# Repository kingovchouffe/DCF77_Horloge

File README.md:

# DCF77_Horloge
 This repos contains the hardware of a DCF77 based clock featuring a STM32F302, an e-ink display, 18650 battery powered with temp humidity and current measurement as well as voltage measurement on the battery.

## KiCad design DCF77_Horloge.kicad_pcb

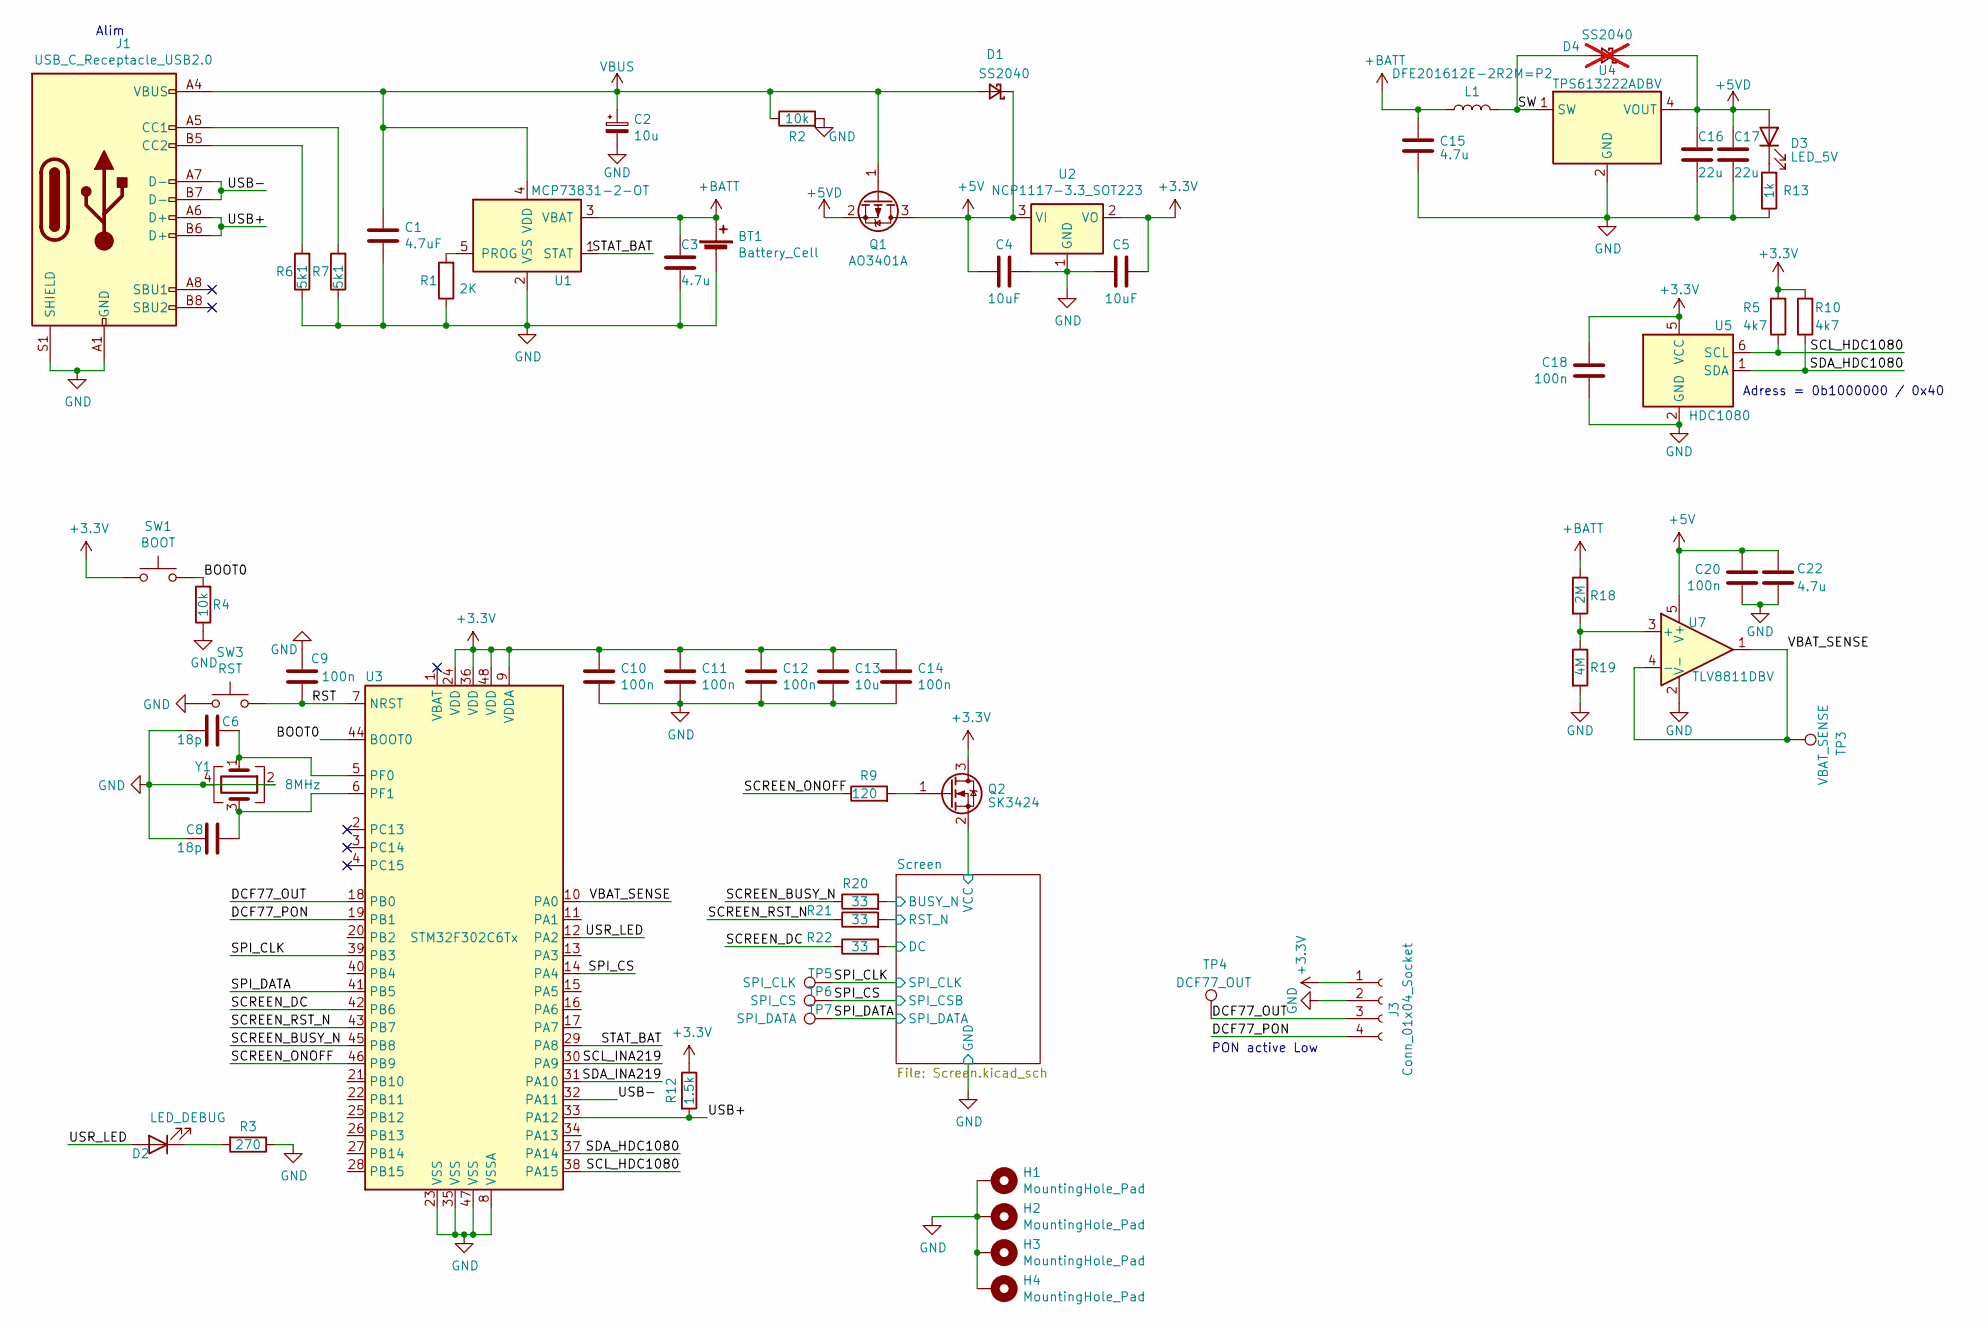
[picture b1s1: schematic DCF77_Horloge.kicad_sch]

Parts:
BT1: Battery_Cell; BatteryHolder_Keystone_1042_1x18650
C1: 4.7uF; C_0603_1608Metric
C2: 10u; CP_Elec_5x5.4
C3, C15, C22: 4.7u; C_0603_1608Metric
C4, C5: 10uF; C_0603_1608Metric
C6, C8: 18p; C_0603_1608Metric
C9, C10, C11, C12, C14, C18, C20: 100n; C_0603_1608Metric
C13: 10u; C_0603_1608Metric
C16, C17: 22u; C_0805_2012Metric
D1: SS2040; D_SOD-123
D2: LED_DEBUG; LED_0603_1608Metric
D3: LED_5V; LED_0603_1608Metric
D4: SS2040; D_SOD-123; not fitted
H1, H2, H3, H4: MountingHole_Pad; MountingHole_3mm_Pad_Via
J1: USB_C_Receptacle_USB2.0; USB_C_Receptacle_GCT_USB4105-xx-A_16P_TopMnt_Horizontal
J3: Conn_01x04_Socket; PinHeader_1x04_P2.54mm_Vertical_SMD_Pin1Left
L1: DFE201612E-2R2M=P2; L_0805_2012Metric_Pad1.15x1.40mm_HandSolder
Q1: AO3401A; SOT-23
Q2: SK3424; SC-59
R1: 2K; R_0603_1608Metric
R2, R4: 10k; R_0603_1608Metric
R3: 270; R_0603_1608Metric
R5, R10: 4k7; R_0603_1608Metric
R6, R7: 5k1; R_0603_1608Metric
R9: 120; R_0603_1608Metric
R12: 1.5k; R_0603_1608Metric
R13: 1k; R_0603_1608Metric
R18: 2M; R_0603_1608Metric
R19: 4M; R_0603_1608Metric
R20, R21, R22: 33; R_0603_1608Metric
SW1: BOOT; SW_SPST_CK_RS282G05A3
SW3: RST; SW_SPST_CK_RS282G05A3
TP3: VBAT_SENSE; TestPoint_Pad_D1.0mm
TP4: DCF77_OUT; TestPoint_Pad_D1.0mm
TP5: SPI_CLK; TestPoint_Pad_D1.0mm
TP6: SPI_CS; TestPoint_Pad_D1.0mm
TP7: SPI_DATA; TestPoint_Pad_D1.0mm
U1: MCP73831-2-OT; SOT-23-5
U2: NCP1117-3.3_SOT223; SOT-223-3_TabPin2
U3: STM32F302C6Tx; LQFP-48_7x7mm_P0.5mm
U4: TPS613222ADBV; SOT-23-5
U5: HDC1080; Texas_PWSON-N6
U7: TLV8811DBV; SOT-23-5
Y1: 8MHz; Crystal_SMD_5032-4Pin_5.0x3.2mm

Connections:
+5V: C4.2, C20.1, C22.1, D1.1 (K), Q1.3 (D), U2.3 (VI), U7.5 (V+)
+5VD: C16.1, C17.1, D3.2 (A), D4.1 (K), Q1.2 (S), U4.4 (VOUT)
+BATT: BT1.1 (+), C3.1, C15.1, L1.1, R18.1, U1.3 (VBAT)
/BOOT0: R4.2, SW1.2, U3.44 (BOOT0)
/DCF77_OUT: J3.3, TP4.1, U3.18 (PB0)
/DCF77_PON: J3.4, U3.19 (PB1)
/RST: C9.1, SW3.2, U3.7 (NRST)
/SCL_HDC1080: R5.1, U3.38 (PA15), U5.6 (SCL)
/SCL_INA219: U3.30 (PA9)
/SCREEN_BUSY_N: R20.1, U3.45 (PB8)
/SCREEN_DC: R22.1, U3.42 (PB6)
/SCREEN_ONOFF: R9.1, U3.46 (PB9)
/SCREEN_RST_N: R21.1, U3.43 (PB7)
/SDA_HDC1080: R10.1, U3.37 (PA14), U5.1 (SDA)
/SDA_INA219: U3.31 (PA10)
/SPI_CLK: TP5.1, U3.39 (PB3); also elsewhere on the board
/SPI_CS: TP6.1, U3.14 (PA4); also elsewhere on the board
/SPI_DATA: TP7.1, U3.41 (PB5); also elsewhere on the board
/STAT_BAT: U1.1 (STAT), U3.29 (PA8)
/SW: D4.2 (A), L1.2, U4.1 (SW)
/Screen/BUSY_N: R20.2; also elsewhere on the board
/Screen/DC: R22.2; also elsewhere on the board
/Screen/RST_N: R21.2; also elsewhere on the board
/USB+: J1.A6 (D+), J1.B6 (D+), R12.2, U3.33 (PA12)
/USB-: J1.A7 (D-), J1.B7 (D-), U3.32 (PA11)
/USR_LED: D2.2 (A), U3.12 (PA2)
/VBAT_SENSE: TP3.1, U3.10 (PA0), U7.1, U7.4 (-)
GND: BT1.2 (-), C1.2, C2.2, C3.2, C4.1, C5.2, C6.2, C8.2, C9.2, C10.2, C11.2, C12.2, C13.2, C14.2, C15.2, C16.2, C17.2, C18.2, C20.2, C22.2, H1.1, H2.1, H3.1, H4.1, J1.A1 (GND), J1.A12 (GND), J1.B1 (GND), J1.B12 (GND), J1.S1 (SHIELD), J3.2, R1.1, R2.2, R3.1, R4.1, R6.1, R7.1, R13.1, R19.2, SW3.1, U1.2 (VSS), U2.1 (GND), U3.8 (VSSA), U3.23 (VSS), U3.35 (VSS), U3.47 (VSS), U4.2 (GND), U5.2 (GND), U7.2 (V-), Y1.2, Y1.4; also elsewhere on the board
unnamed: D2.1 (K), R3.2
unnamed: D3.1 (K), R13.2
unnamed 31: Q2.2 (S); also elsewhere on the board
unnamed: J1.A5 (CC1), R7.2
unnamed: J1.B5 (CC2), R6.2
unnamed: R1.2, U1.5 (PROG)
unnamed: C6.1, U3.5 (PF0), Y1.1
unnamed: C8.1, U3.6 (PF1), Y1.3
unnamed: R18.2, R19.1, U7.3 (+)
VBUS: C1.1, C2.1, D1.2 (A), J1.A4 (VBUS), J1.A9 (VBUS), J1.B4 (VBUS), J1.B9 (VBUS), Q1.1 (G), R2.1, U1.4 (VDD)

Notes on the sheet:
PON active Low
Adress = 0b1000000 / 0x40
Alim

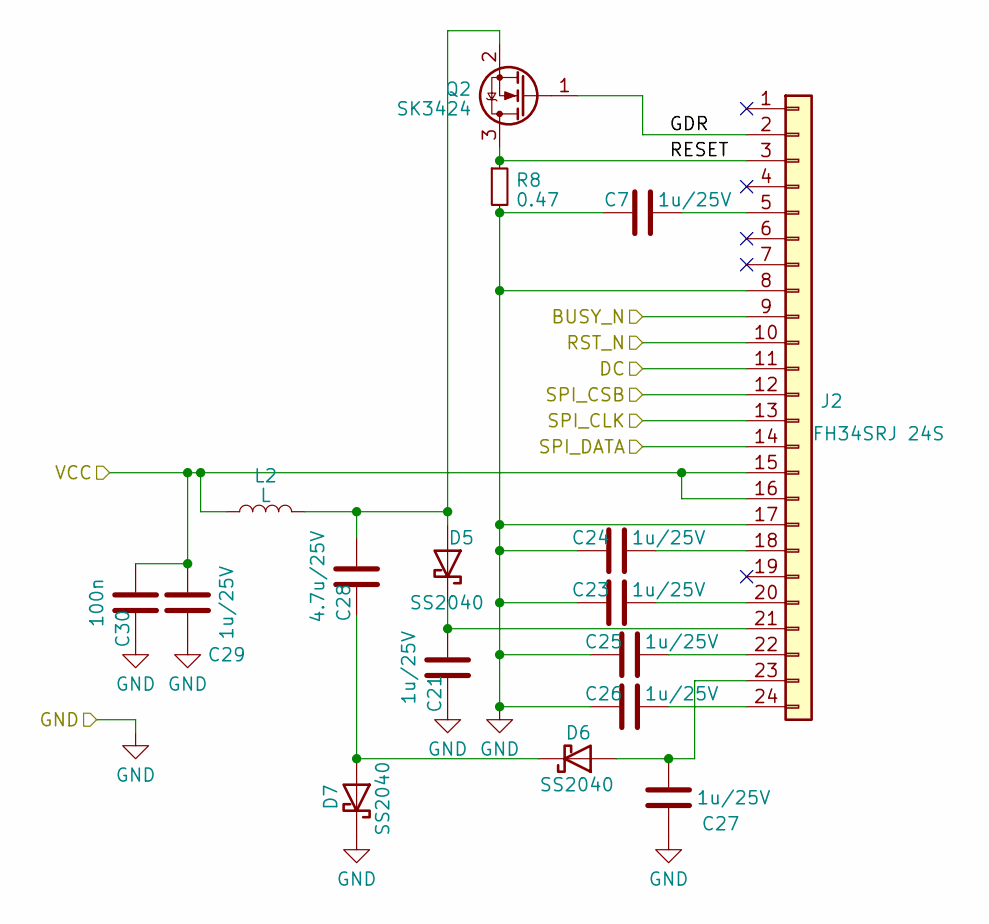
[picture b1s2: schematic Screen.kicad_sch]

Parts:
C7, C21, C23, C24, C25, C26, C27, C29: 1u/25V; C_0603_1608Metric
C28: 4.7u/25V; C_0603_1608Metric
C30: 100n; C_0603_1608Metric
D5, D6, D7: SS2040; D_SOD-123
J2: FH34SRJ 24S; HRS_FH34SRJ-24S-0.5SH(99)
L2: L; L_1210_3225Metric
Q2: SK3424; SC-59
R8: 0.47; R_0603_1608Metric

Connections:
/SPI_CLK: J2.13; also elsewhere on the board
/SPI_CS: J2.12; also elsewhere on the board
/SPI_DATA: J2.14; also elsewhere on the board
/Screen/BUSY_N: J2.9; also elsewhere on the board
/Screen/DC: J2.11; also elsewhere on the board
/Screen/RST_N: J2.10; also elsewhere on the board
/Screen/VCC: C29.2, C30.2, J2.15, J2.16, L2.1; also elsewhere on the board
GND: C7.1, C21.1, C23.1, C24.1, C25.1, C26.1, C27.1, C29.1, C30.1, D7.1 (K), J2.8, J2.17, R8.2; also elsewhere on the board
unnamed: C28.2, D5.2 (A), L2.2, Q2.2 (S)
unnamed: C21.2, D5.1 (K), J2.21
unnamed: C27.2, D6.2 (A), J2.23
unnamed: C28.1, D6.1 (K), D7.2 (A)
unnamed: C7.2, J2.5
unnamed: C24.2, J2.18
unnamed: C23.2, J2.20
unnamed: C25.2, J2.22
unnamed: C26.2, J2.24

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
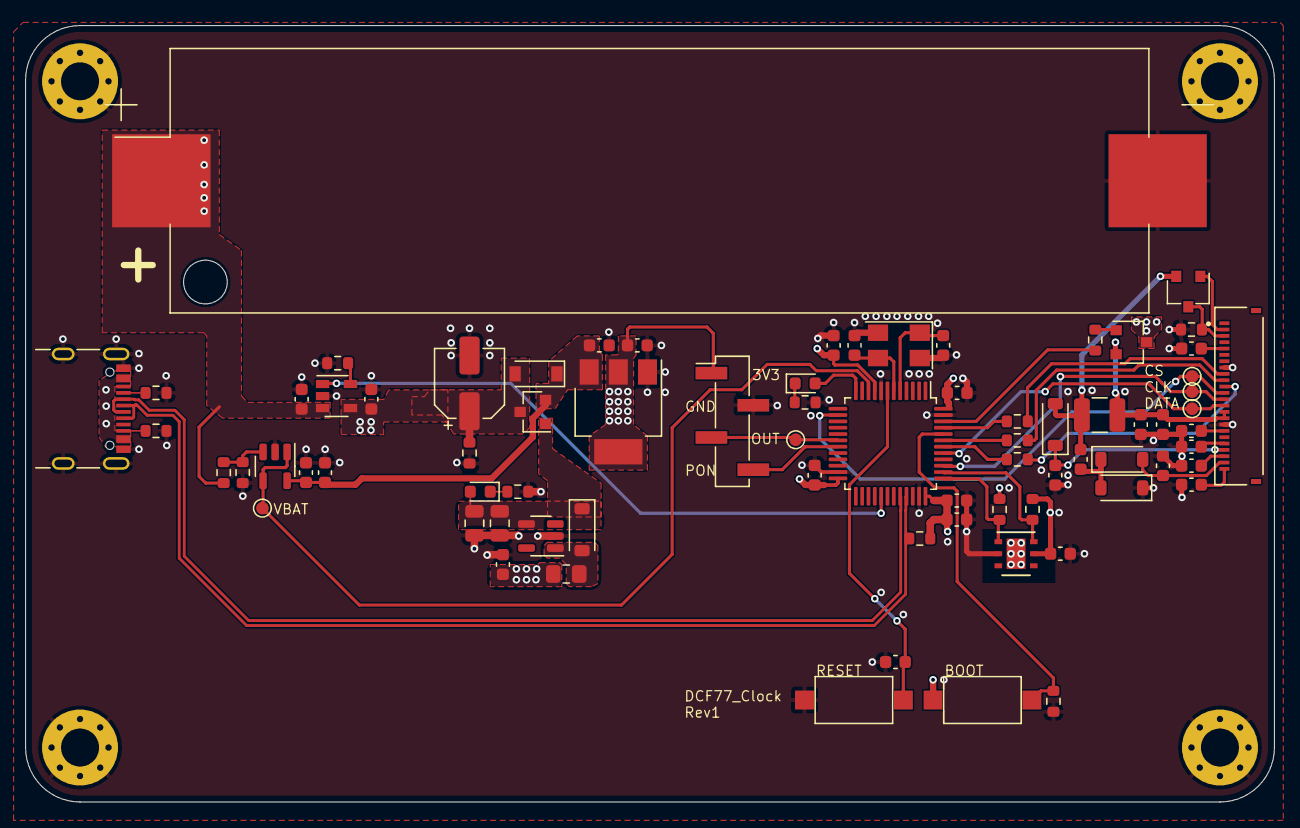
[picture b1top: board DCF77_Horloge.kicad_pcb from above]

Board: 4 copper layers, 98.6 x 61.3 mm, 80 parts (0 on the bottom side), 49 nets.

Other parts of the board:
Q3: SK3424; SC-59

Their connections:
/Screen/VCC: Q3.2 (S); also elsewhere on the board

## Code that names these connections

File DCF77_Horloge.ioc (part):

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Mcu.Name=STM32F302C(6-8)Tx
Mcu.Package=LQFP48
Mcu.UserName=STM32F302C8Tx
PA0.Mode=IN1-Single-Ended
PA0.Signal=ADC1_IN1
PA10.Mode=I2C
PA10.Signal=I2C2_SDA
PA11.Mode=Device
PA11.Signal=USB_DM
PA12.Mode=Device
PA12.Signal=USB_DP
PA14.Mode=I2C
PA14.Signal=I2C1_SDA
PA15.Mode=I2C
PA15.Signal=I2C1_SCL
PA4.Mode=NSS_Signal_Hard_Output
PA4.Signal=SPI3_NSS
PA9.Mode=I2C
PA9.Signal=I2C2_SCL
PB0.GPIOParameters=GPIO_PuPd,GPIO_Label
PB0.GPIO_Label=DCF_IN
PB0.GPIO_PuPd=GPIO_PULLUP
PB0.Signal=GPIO_Input
PB10.Mode=Asynchronous
PB10.Signal=USART3_TX
PB11.Mode=Asynchronous
PB11.Signal=USART3_RX
PB3.Mode=Simplex_Bidirectional_Master
PB3.Signal=SPI3_SCK
PB5.Mode=Simplex_Bidirectional_Master
PB5.Signal=SPI3_MOSI
PB6.Signal=GPIO_Output
PB7.Signal=GPIO_Output
PB8.Signal=GPIO_Output
PB9.Signal=GPIO_Output
PF0-OSC_IN.Mode=HSE-External-Oscillator
PF0-OSC_IN.Signal=RCC_OSC_IN
PF1-OSC_OUT.Mode=HSE-External-Oscillator
PF1-OSC_OUT.Signal=RCC_OSC_OUT
RCC.HSEPLLFreq_Value=8000000
RCC.HSE_VALUE=8000000
RCC.SYSCLKFreq_VALUE=72000000
RCC.SYSCLKSourceVirtual=RCC_SYSCLKSOURCE_PLLCLK
board=custom

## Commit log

2021-08-23 Add pull up for i2c and change layout
2021-10-14 change MCU from RP2040 to ESP32-WROOM-32
2021-11-07 mod with esp 32
2022-05-27 some changes
2023-05-03 big update
2023-05-03 update pdf
2023-05-08 routing
2023-05-08 tbd diff pair config
2023-06-04 board to fab
